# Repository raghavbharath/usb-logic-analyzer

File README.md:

# ECE692 Final Project - USB Digital Logic Analyzer

Main repository: https://github.com/ragusauce4357/ece692-final-project

**Group Members:** Raghav Bharathan (raghavbharath), Arnav Revankar (avr34), Gonzalo Villanueva, William Dougherty (Will35084), Bryan Galecio (bryangalecio04)

This project is a custom USB logic analyzer built around two STM32F446RE Nucleo boards, developed as our final project for ECE 692 at NJIT. The system captures digital signals from an external device under test, decodes UART, SPI, I2C, and CAN protocols using a Go signal decoder, and visualizes the results in real time through a Python GUI.

## How It Works

The transmitter Nucleo generates test signals over UART, SPI, I2C, and CAN. The receiver Nucleo samples up to 8 digital channels simultaneously at 1MHz using DMA-driven GPIO capture, packages the raw samples into packets, and streams them to a host PC over USB CDC. A Go application reads the packet stream, decodes UART, SPI, and I2C from the raw samples, and forwards the results to a Python GUI over TCP. CAN frames are decoded inside the STM32 hardware itself by the bxCAN peripheral and forwarded directly. 

## Repository and Branch Structure

Note: This repository is organized across several feature branches, with each of us making contributions in different areas. The `master` branch contains the integrated codebase including the firmware configured for 10kHz sampling over ST-Link USART, which was used during final testing and demonstration. The 1MHz USB CDC configuration and other work can be found in the individual feature branches (`feature/stm32-firmware`, `feature/SignalDecoder`, `feature/GUI`, `feature/PCB`, `feature/3DEnclosure`). The `feature/test` branch contains the final snapshot used during the live demo.

```
firmware-receiver/     # STM32 receiver firmware (STM32CubeIDE)
firmware-transmitter/  # STM32 transmitter firmware
SignalDecoder/         # Go signal decoder application
gui/src/               # Python GUI
PCB/                   # KiCad schematic and PCB layout
enclosure/             # 3D printable STL files
docs/                  # Datasheets and reference manuals
```

### Firmware

The receiver firmware runs on an STM32F446RE at 168MHz. TIM1 generates a 1MHz update event that triggers DMA2 on each tick. The DMA reads the lower byte of GPIOC (PC0-PC7) into a 1024-byte circular ping-pong buffer. When the first half fills, an interrupt fires and the firmware packages bytes 0-511 into a 516-byte logic packet with a 2-byte header, sequence number, and XOR checksum, then sends it over USB CDC. The second half fires the same way. This design keeps sampling continuous with no gaps.

CAN is handled separately. The bxCAN peripheral runs at 500kbps and decodes incoming frames entirely in hardware, delivering a clean frame (ID, DLC, data bytes) to an RX interrupt handler. The firmware packages this into a variable-length CAN packet and sends it over USB CDC alongside the logic packets.

The transmitter firmware runs the same clock config and outputs test signals in a loop every second: UART at 115200 baud, SPI at ~164kHz, I2C to a dummy address (0x52), and a CAN frame with ID 0x123 and payload `0xCAFEBABEDEADBEEF`.

Packet formats:
- Logic: `[0xAA][0xBB][seq][512 bytes][XOR checksum]` = 516 bytes
- CAN: `[0xCC][0xDD][seq][ID_H][ID_L][DLC][0-8 data bytes][XOR checksum]` = variable length

### Go SignalDecoder

The SignalDecoder reads the USB serial stream from the receiver. A `ReadByteStream` goroutine reads into a 1024-byte buffer and pushes raw byte slices into a buffered channel. A `Run` coordinator consumes from the channel, scans for `0xAA 0xBB` or `0xCC 0xDD` headers using a pending accumulation slice to handle packets that span across reads, validates XOR checksums, and detects dropped packets via sequence number wraparound. Logic packets go to the UART, SPI, and I2C decoders. CAN packets are forwarded directly to Python over TCP.

CLI flags: `--port`, `--protocol`, `--pins`, `--duration`

### Python GUI

The GUI launches the Go binary as a subprocess with the appropriate CLI arguments, then connects to its TCP socket to receive decoded data. A background thread parses incoming packets and emits Qt signals to the main thread.

The waveform view shows 8 digital channels plus a synthetic CAN row reconstructed from decoded frame timestamps and DLC. Features include a crosshair cursor, a permanent multi-pair measurement tool with delta-time and frequency readout, a vertical scrollbar, protocol decode annotations color-coded by type, and a CAN decode table. Captures can be saved and loaded as JSON.

Run in simulator mode (no hardware needed, but a few tweaks might need to be made to the code):
```
python gui/src/gui.py --test
```

### PCB

The PCB is a breakout shield that plugs onto both Nucleo boards simultaneously via their morpho headers. It carries a TXS0108E 8-channel bidirectional level shifter for the probe inputs, two SN65HVD230 CAN transceivers (one per Nucleo), per-channel 1kohm series resistors and BAT85 Schottky diodes for overvoltage protection, 4.7kohm I2C pull-ups, a 10-pin probe header, a CANH/CANL screw terminal, and 120ohm CAN termination resistors at each bus end. The schematic is split into receiver and transmitter sub-sheets under a hierarchical root sheet in KiCad.

### Enclosure

3D-printable STL files for a custom enclosure are in `enclosure/`.

## Dependencies

Python:
```
pip install -r gui/src/requirements.txt
```

Go:
```
cd SignalDecoder && go build
```

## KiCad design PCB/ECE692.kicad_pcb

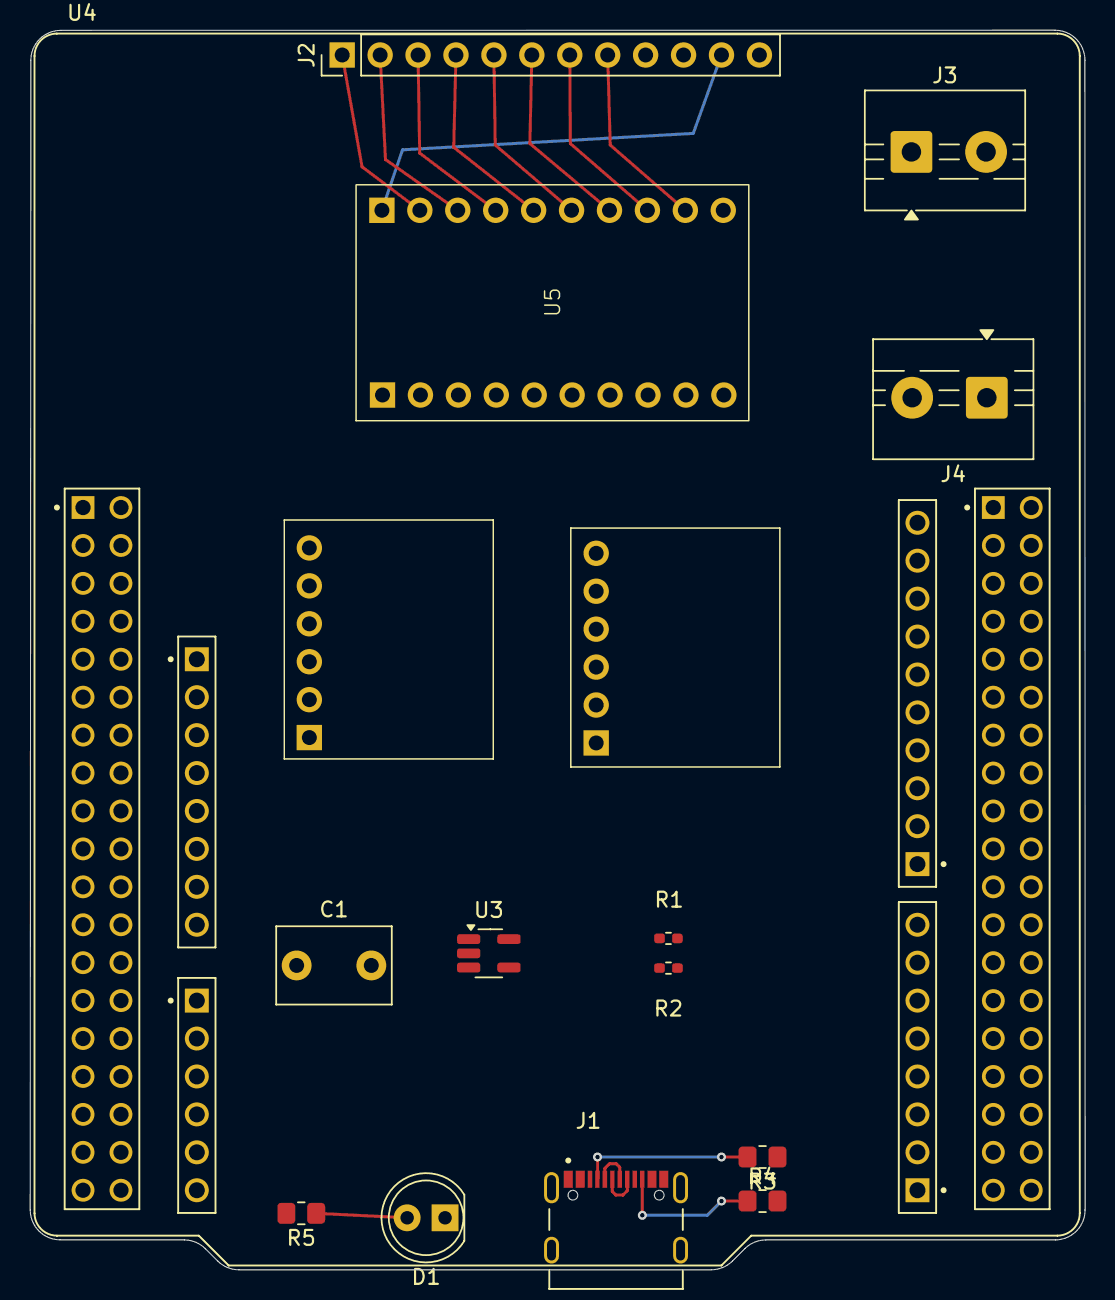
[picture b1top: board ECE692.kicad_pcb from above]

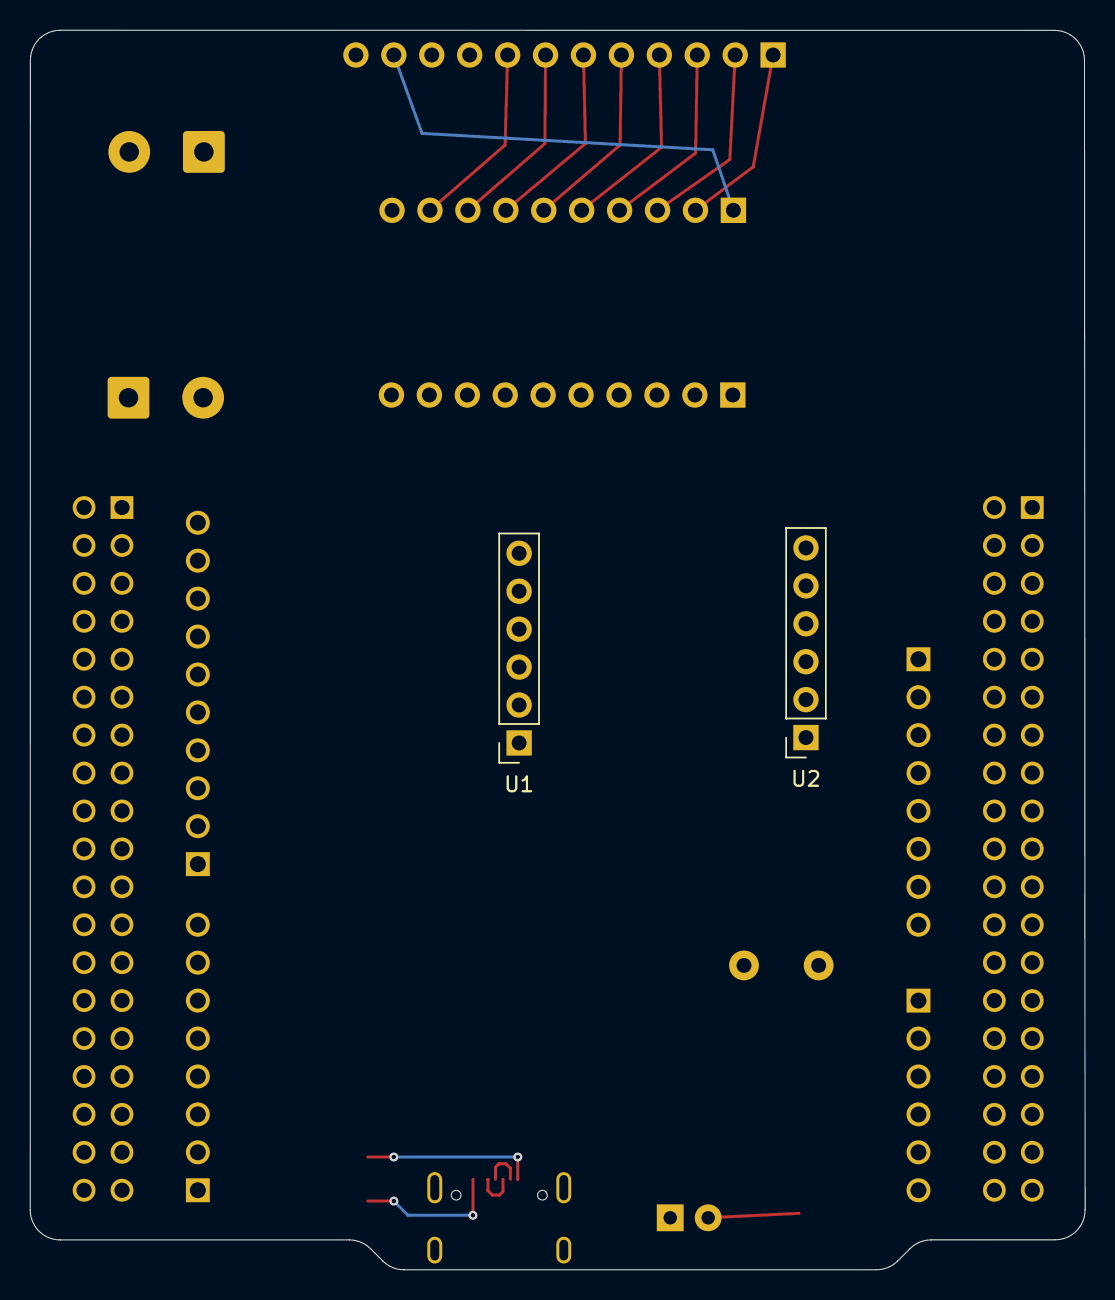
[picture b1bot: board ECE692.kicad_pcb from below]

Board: 2 copper layers, 70.6 x 83.0 mm, 16 parts (2 on the bottom side), 22 nets.

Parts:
C1: 1uF; C_Disc_D7.5mm_W5.0mm_P5.00mm
D1: LED; LED_D5.0mm
J1: TYPE-C_16PIN_2MD__073_; SHOUHAN_TYPE-C_16PIN_2MD__073_
J2: Conn_01x12; PinHeader_1x12_P2.54mm_Vertical
J3, J4: Screw_Terminal_01x02; TerminalBlock_MaiXu_MX126-5.0-02P_1x02_P5.00mm
R1: 17k; R_0402_1005Metric_Pad0.72x0.64mm_HandSolder
R2: 10k; R_0402_1005Metric_Pad0.72x0.64mm_HandSolder
R3, R4: 5.1k; R_0805_2012Metric_Pad1.20x1.40mm_HandSolder
R5: 150; R_0805_2012Metric_Pad1.20x1.40mm_HandSolder
U1: CAN_BUS_TRANSCEIVER1; PinSocket_1x06_P2.54mm_Vertical
U2: CAN_BUS_TRANSCEIVER2; PinSocket_1x06_P2.54mm_Vertical
U3: LOD; SOT-23-5_HandSoldering
U4: STM32F446RETx; MODULE_NUCLEO-F446RE
U5: LEVEL_SHIFTER

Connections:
3V3: C1.1, R1.1, U1.1 (3V3), U2.1 (3V3), U3.5 (VOUT), U5.1 (VCCA), U5.10 (OE)
CRX_TB: J2.10, U1.3 (CTX)
CTX_TB: J2.9, U1.4 (CRX)
D+: J1.A6 (DP1), J1.B6 (DP2)
D-: J1.A7 (DN1), J1.B7 (DN2)
GND: C1.2, D1.1 (K), J1.A1_B12 (GND_A), J1.B1_A12 (GND_B), J1.SH1 (SHIELD), J1.SH2 (SHIELD), J1.SH3 (SHIELD), J1.SH4 (SHIELD), J2.12, R2.2, R3.1, R4.2, U1.2 (GND), U2.2 (GND), U3.2 (GND), U5.20 (GND)
unnamed: D1.2 (A), R5.1
unnamed: J1.A5 (CC1), R3.2
unnamed: J1.B5 (CC2), R4.1
unnamed: J3.1, J4.1, U1.5 (CANH), U2.5 (CANH)
unnamed: J3.2, J4.2, U1.6 (CANL), U2.6 (CANL)
unnamed: R1.2, R2.1, U3.4 (ADJ)
TB_CH1: J2.1, U5.12 (B1)
TB_CH2: J2.2, U5.13 (B2)
TB_CH3: J2.3, U5.14 (B3)
TB_CH4: J2.4, U5.15 (B4)
TB_CH5: J2.5, U5.16 (B5)
TB_CH6: J2.6, U5.17 (B6)
TB_CH7: J2.7, U5.18 (B7)
TB_CH8: J2.8, U5.19 (B8)
VBUS: J1.A4_B9 (VBUS_A), J1.B4_A9 (VBUS_B), U3.1 (5V), U3.3 (EN)
V_TB: J2.11, U5.11 (VCCB)

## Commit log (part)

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2026-04-09 Added preliminary list of stuff we need.
    - List was generated using Claude
    - We have read it through and pruned/added items
    - Yet to be reviewed by the rest of the group
2026-04-09 added markdown to html conversion script
2026-04-09 added gitignore
2026-04-10 removed PCA9309 from list
2026-04-10 added docs for the F446RE
2026-04-10 added F401 datasheets and renamed the others
2026-04-10 fixed folder name
2026-04-13 added initial Software.ioc file from CubeMX
2026-04-13 added changelog for firmware
2026-04-14 Finished the CubeMX configuration.
2026-04-14 Generated the HAL code and drivers with CubeMX
2026-04-14 updated the changelog
2026-04-15 updated gitignore
2026-04-15 Changes to the STM32 receiver CubeMX config
2026-04-15 Added a Draw.io file, hopefully it helps to visualize the setup a little better
2026-04-16 added a Doxyfile
2026-04-16 added initial generated docs. No code written yet.
2026-04-19 Updated the doxyfile, and regenerated the docs.
    - Set to NO LATEX or MAN PAGES generation.
    - Set other random bits n bobs too.
    - Set the PREDEFINED to the ifdefs which are used within HAL libraries
2026-04-20 Added some firmware code: double buferring and CAN bus packet framing and decoding
2026-04-20 updated changelog
2026-04-20 fixed a USB CDC declaration error
2026-04-20 Squashed 'SignalDecoder/' content from commit 934ee15
    git-subtree-dir: SignalDecoder
    git-subtree-split: 934ee15288aa228c6215f0bd2fbcf29d99eb0276
2026-04-20 Modified the go source files for new module name
    - Old was github.com/avr34/SignalDecoder
    - New is github.com/ragusauce4357/ECE692-Final-Project/SignalDecoder
2026-04-20 Initial GUI implementation. Basic stuff, haven't even finished the decoder yet, so still need to work on it
2026-04-20 Removed firmware and metadata files from this branch
2026-04-20 Organized file structure
2026-04-21 added initial Kicad project
2026-04-21 added and updated changelog
2026-04-22 added some datasheets for pcb
    - Added datasheets for the LDO, USB connector, and USB dp/dm filter
2026-04-22 replaced the USBC datasheet
2026-04-22 updated the USBC datasheet again, made a mistake last time
2026-04-23 added the CAN transceiver symbol
2026-04-23 added datasheets for the can transceiver and level shifter
2026-04-23 Initial Python GUI updates including TCP socket connection to the eventual Go decoder as well as a display for the GUI. Feel free to try it out. I'll update the CHANGELOG soon.
2026-04-24 Added a clear option for two measurements, made the vertical markers cleaner, it just looks a little neater now. shoutout to Jean Claude
2026-04-24 removed PCB folder from the GUI branch
2026-04-25 Added the completed schematic, and initial PCB.
    - Schematic is complete, and also most footprint assignment
    - Still need to put the morpho connectors on PCB, and route channels
2026-04-25 Update CHANGELOG with GUI enhancements
    Updated CHANGELOG with new features and changes for the GUI, including a blue checkmark for checkboxes, improved resizing behavior, and tabbed panels.
2026-04-25 Modified some stuff, and did some routing
    - Replaced the rectangle with the STM nucleo board shape
    - added the level shifter symbol and footprint
2026-04-25 Changed the DMA data width to half-word. Checkout the reasoning in the CHANGELOG. Updated some firmware code accordingly, using a packet size of 1028 now.
2026-04-25 Removed the .metadata from tracking, added .gitignore. We need a folder for Software/Transmitter thats why.
2026-04-25 Changed Software/ to firmware-receiver/. Added a firmware-transmitter/ folder so we can work on it. Just did initial pin and clock configurations.
2026-04-25 updated gitignore. misspelled metadata last time :(
2026-04-25 fixed gitignores, file structure should be good
2026-04-25 added a CHANGELOG for transmitter firmware.
2026-04-26 added cli argument to list available ports
2026-04-26 Moved status LED to PC8 and shifted the channels down to PC0-PC7. Reverted the code back to DMA byte data width and changed accordingly.
2026-04-26 Added Debug, Release, and .metadata to .gitignore
2026-04-26 Completed the transmitter code for simulating packets for all 4 protocols.
2026-04-27 Added initial code for serial package. IT DOESN'T WORK YET!
    - Added a function that runs as a goroutine and forwards data to channel
    - Also added a temporary verification function, but some reason it
    doesn't print??? Not sure why
2026-04-27 added a changelog
2026-04-27 Update serial parser, config, and test scripts to match packet protocol
2026-04-28 Fixed sequence tracking, got the test scripts working with Arnav's socat script. I'll add a small sample of the output in the CHANGELOG.
2026-04-28 Finished the PCB
    - Finished the PCB and ordered at JLCPCB
    - Uploaded schematic pdf, and image of complete layout and routing
2026-04-28 added the gerber files
2026-04-29 added the SPI decoder with custom SPI modes and optional CS support
2026-04-29 updated serial.go to accomodate for spi decoder.
2026-04-29 Added docs for how uart decoder works
2026-04-29 Added Sample Rate as required cli argument
    - pass in using `-sr xyz`
2026-04-29 Added the initial UART decoder. Haven't tested fully if it works yet
2026-05-01 deleted pycache in gui
2026-05-01 updated test.py to support SPI testing and made a few tweaks to the SPI decoder. There was a slight masking issue in the UART decoder, so fixed that as well.
2026-05-01 removed capture test binary file.
2026-05-01 updated the changelog to be upto date with commit 7f6f4b4
2026-05-02 added 'baud' cli argument to specify transmitter baud
2026-05-02 use this for testing WITHOUT the usb
2026-05-02 updated delay timeout
2026-05-02 changed baud rate of transmitter to 9600
2026-05-02 added LED toggles
2026-05-02 updated the serial.go with correct bounds.
2026-05-04 added the i2c decoder. it works but with only 1 sample per half as opposed to 5. Also added the i2c and spi to generate_bin so we can see the raw bytes.
2026-05-04 Add files via upload
    font size bigger
2026-05-04 Delete gui/display.py
    oops
2026-05-04 Delete gui/gui.py
    oops
2026-05-06 changed transmitter baud rate to 2400, it works. cannot go any higher for st-link usart testing.
2026-05-06 updated files
2026-05-06 merged signal decoder stuff into test.
2026-05-06 merged gui stuff into test.
2026-05-06 fixed a bunch of packet alignment issues, sequence number cycle back issue, timestamp problems, etc. sample output looks solid, but if we want to eliminate even more noise fluctuations, we have to sa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
2026-05-06 drawio file
2026-05-06 got the GUI to display uart signals, tho not very reliable rn. the decoded frames dont show yet. Added a few things. We can now forward raw logic packets and ANN decoded frames from Go to Python over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
2026-05-06 made a few changes to the glitch filter and decoded frames display. it now shows the annotations on top of the waveforms, and it seems to be mostly correct.
2026-05-06 final block diagrams
2026-05-06 added the go binary file and pushed other updates
2026-05-08 added final changes that were used during testing, including the slideshow presentation.
2026-05-08 fixed slideshow format and added updated GUI picture.
2026-05-08 added enclosure and lid STL files.
2026-05-08 untracked and removed a few files.
2026-05-08 updated README and added enclosure files.
2026-05-08 updated README.
2026-05-08 added gitattributes.
2026-05-14 Update README
    Corrected the order of group members in the README.
2026-05-14 updated README
    Updated group member names with GitHub usernames and modified repository link format.
2026-05-14 updated README
    Updated project details, added packet protocol, file structure, CLI flags, build instructions, and testing notes.
2026-05-19 Add MIT License to the project
